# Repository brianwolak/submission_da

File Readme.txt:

Student Name: Brian Wolak

NSHE ID#: 2000509437

Student Email: wolak@unlv.nevada.edu

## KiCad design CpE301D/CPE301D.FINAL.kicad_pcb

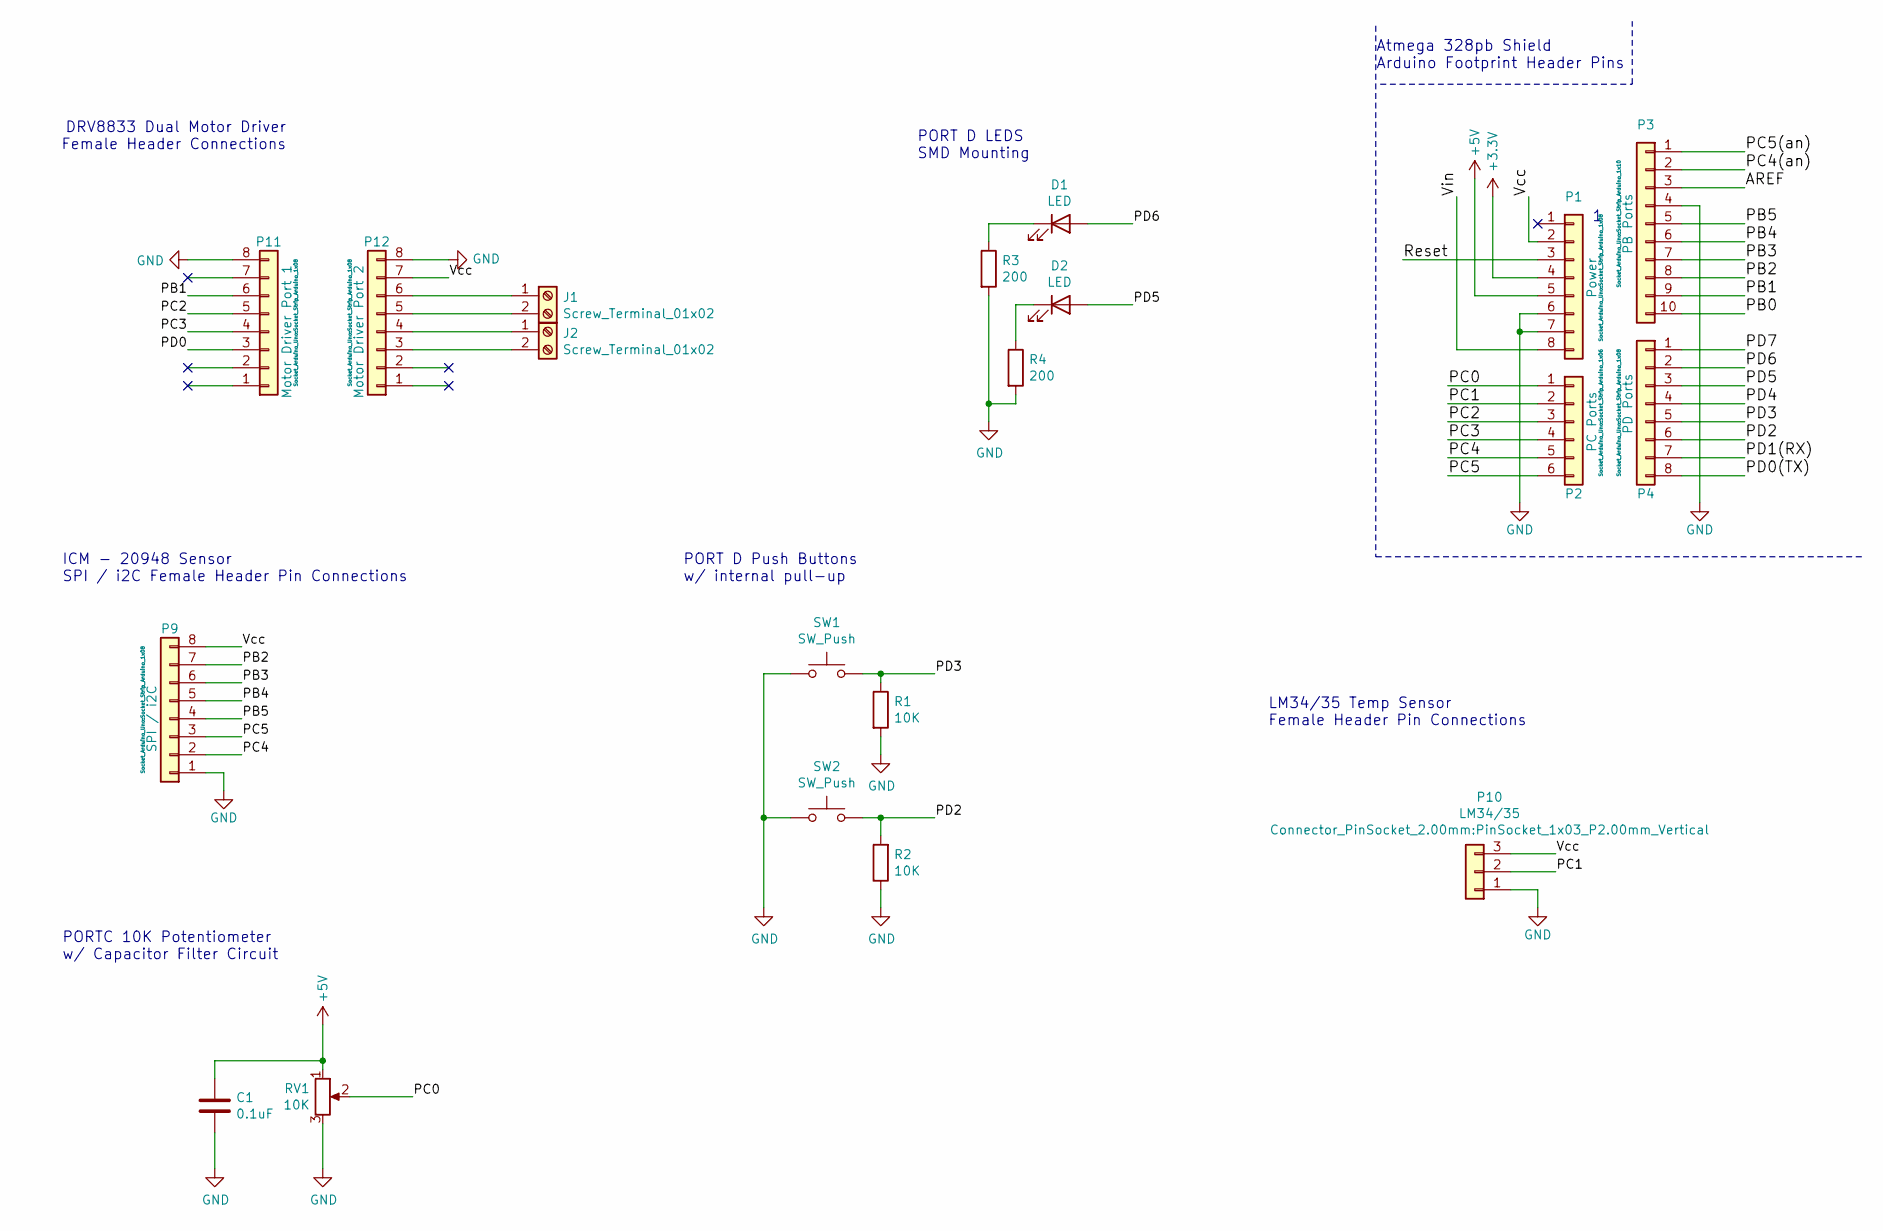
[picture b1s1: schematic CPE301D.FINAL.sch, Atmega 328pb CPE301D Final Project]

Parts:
C1: 0.1uF; C_0805_2012Metric_Pad1.18x1.45mm_HandSolder
D1, D2: LED; LED_1206_3216Metric
J1, J2: Screw_Terminal_01x02; TerminalBlock_Phoenix_MKDS-3-2-5.08_1x02_P5.08mm_Horizontal
P1: Power; Socket_Strip_Arduino_1x08
P2: PC Ports; Socket_Strip_Arduino_1x06
P3: PB Ports; Socket_Strip_Arduino_1x10
P4: PD Ports; Socket_Strip_Arduino_1x08
P9: SPI / i2C; Socket_Strip_Arduino_1x08
P10: LM34/35; PinSocket_1x03_P2.00mm_Vertical
P11: Motor Driver Port 1; Socket_Strip_Arduino_1x08
P12: Motor Driver Port 2; Socket_Strip_Arduino_1x08
R1, R2: 10K; R_2010_5025Metric
R3, R4: 200; R_2010_5025Metric
RV1: 10K; Potentiometer_Bourns_3296Y_Vertical
SW1, SW2: SW_Push; SW_SPST_B3U-1000P

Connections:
+3V3: P1.4
+5V: C1.1, P1.5, RV1.1
/AREF: P3.3
/PB0: P3.10
/PB1: P3.9, P11.6
/PB2: P3.8, P9.7
/PB3: P3.7, P9.6
/PB4: P3.6, P9.5
/PB5: P3.5, P9.4
/PC0: P2.1, RV1.2
/PC1: P2.2, P10.2
/PC2: P2.3, P11.5
/PC3: P2.4, P11.4
/PC4: P2.5, P9.2
/PC4(an): P3.2
/PC5: P2.6, P9.3
/PC5(an): P3.1
/PD0: P11.3
/PD0(TX): P4.8
/PD1(RX): P4.7
/PD2: P4.6, R2.2, SW2.2
/PD3: P4.5, R1.1, SW1.2
/PD4: P4.4
/PD5: D2.2 (A), P4.3
/PD6: D1.2 (A), P4.2
/PD7: P4.1
/Reset: P1.3
/Vcc: P1.2, P9.8, P10.3, P12.7
/Vin: P1.8
GND: C1.2, P1.6, P1.7, P3.4, P9.1, P10.1, P11.8, P12.8, R1.2, R2.1, R3.2, R4.2, RV1.3, SW1.1, SW2.1
unnamed: D1.1 (K), R3.1
unnamed: D2.1 (K), R4.1
unnamed: J1.1, P12.6
unnamed: J1.2, P12.5
unnamed: J2.1, P12.4
unnamed: J2.2, P12.3

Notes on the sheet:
Atmega 328pb Shield Arduino Footprint Header Pins
PORT D LEDS SMD Mounting
PORTC 10K Potentiometer w/ Capacitor Filter Circuit
PORT D Push Buttons w/ internal pull-up
LM34/35 Temp Sensor Female Header Pin Connections
ICM - 20948 Sensor SPI / i2C Female Header Pin Connections
DRV8833 Dual Motor Driver Female Header Connections

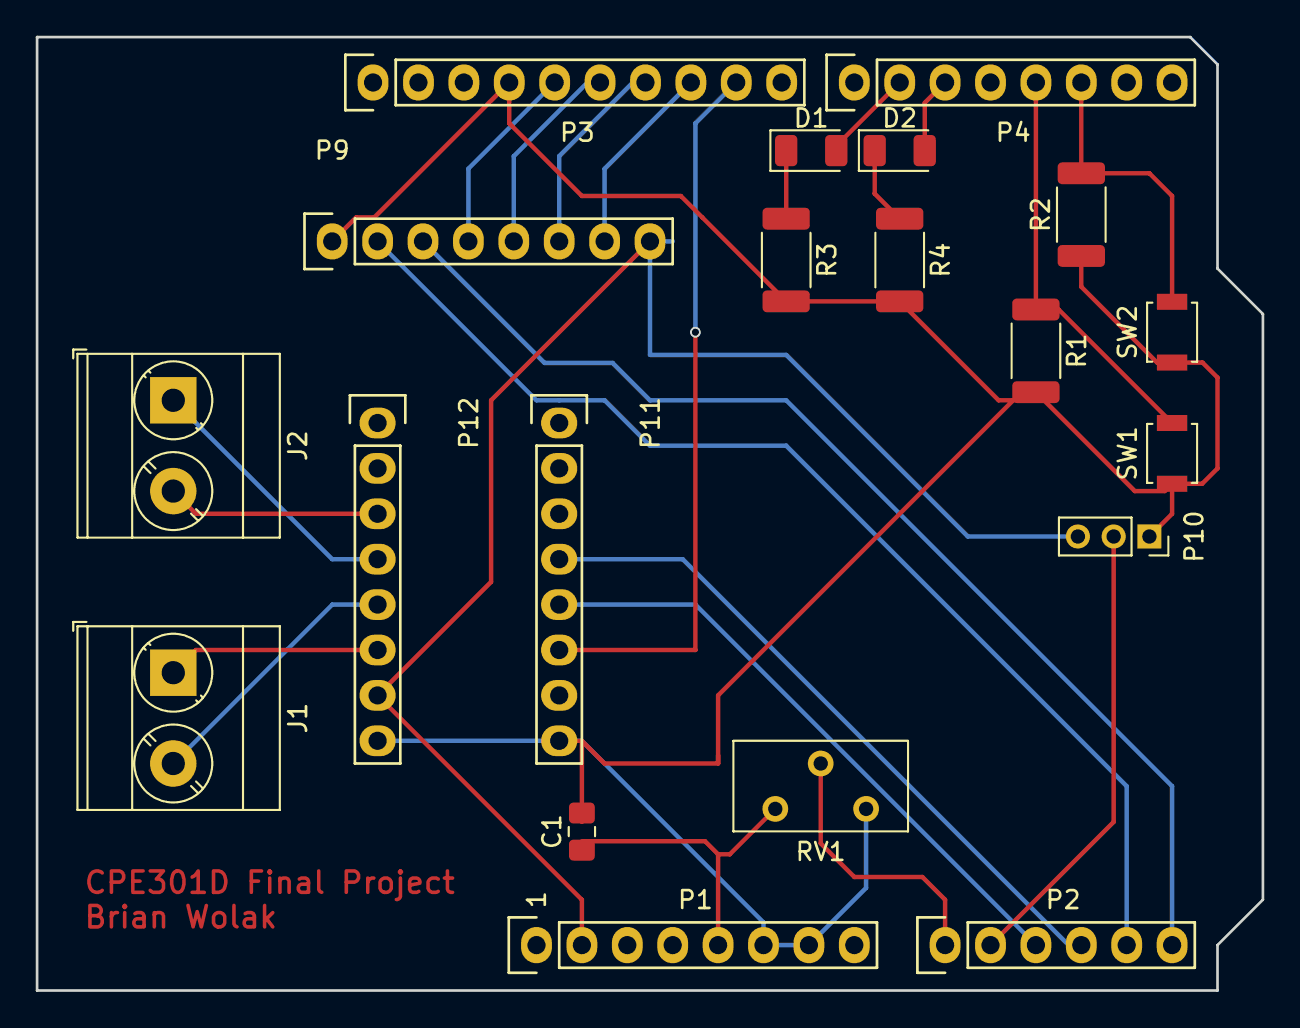
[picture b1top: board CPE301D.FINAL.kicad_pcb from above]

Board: 2 copper layers, 68.6 x 53.3 mm, 20 parts (0 on the bottom side), 24 nets.
